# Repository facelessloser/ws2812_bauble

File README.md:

# ws2812_bauble
ws2812_bauble

Blog post - https://facelesstech.wordpress.com/2020/11/29/ws2812-xmas-bauble/
Youtube - https://youtu.be/SUzfvS8YYB8

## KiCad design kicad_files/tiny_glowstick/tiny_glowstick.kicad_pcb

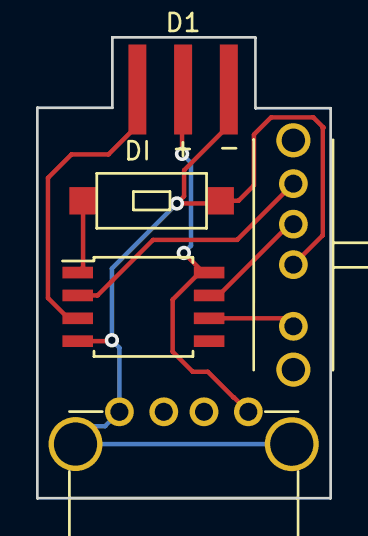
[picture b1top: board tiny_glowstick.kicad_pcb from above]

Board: 2 copper layers, 16.3 x 25.6 mm, 5 parts (0 on the bottom side), 7 nets.

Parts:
D1: WS2812B; APA-106_custom_wider
J1: USB_A; male_usb_custom
SW1: SW_SP3T; 3_way_switch
SW2: SW_Push; SMD_2pin_button_custom
U1: ATtiny85-20PU; SOIJ-8_5.3x5.3mm_P1.27mm

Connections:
unnamed: D1.1, J1.1, U1.8
unnamed: D1.3, J1.4, SW1.3, SW2.2, U1.4
unnamed: D1.4, U1.3
unnamed: SW1.1, U1.2
unnamed: SW1.2, U1.7
unnamed: SW1.4, U1.6
unnamed: SW2.1, U1.1

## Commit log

2020-11-29 3d printed files
2020-11-29 arduino files
2020-11-29 kicad files
2020-11-29 photo
2020-11-29 added photo
2020-11-29 added photo1
2020-11-29 added photo2
